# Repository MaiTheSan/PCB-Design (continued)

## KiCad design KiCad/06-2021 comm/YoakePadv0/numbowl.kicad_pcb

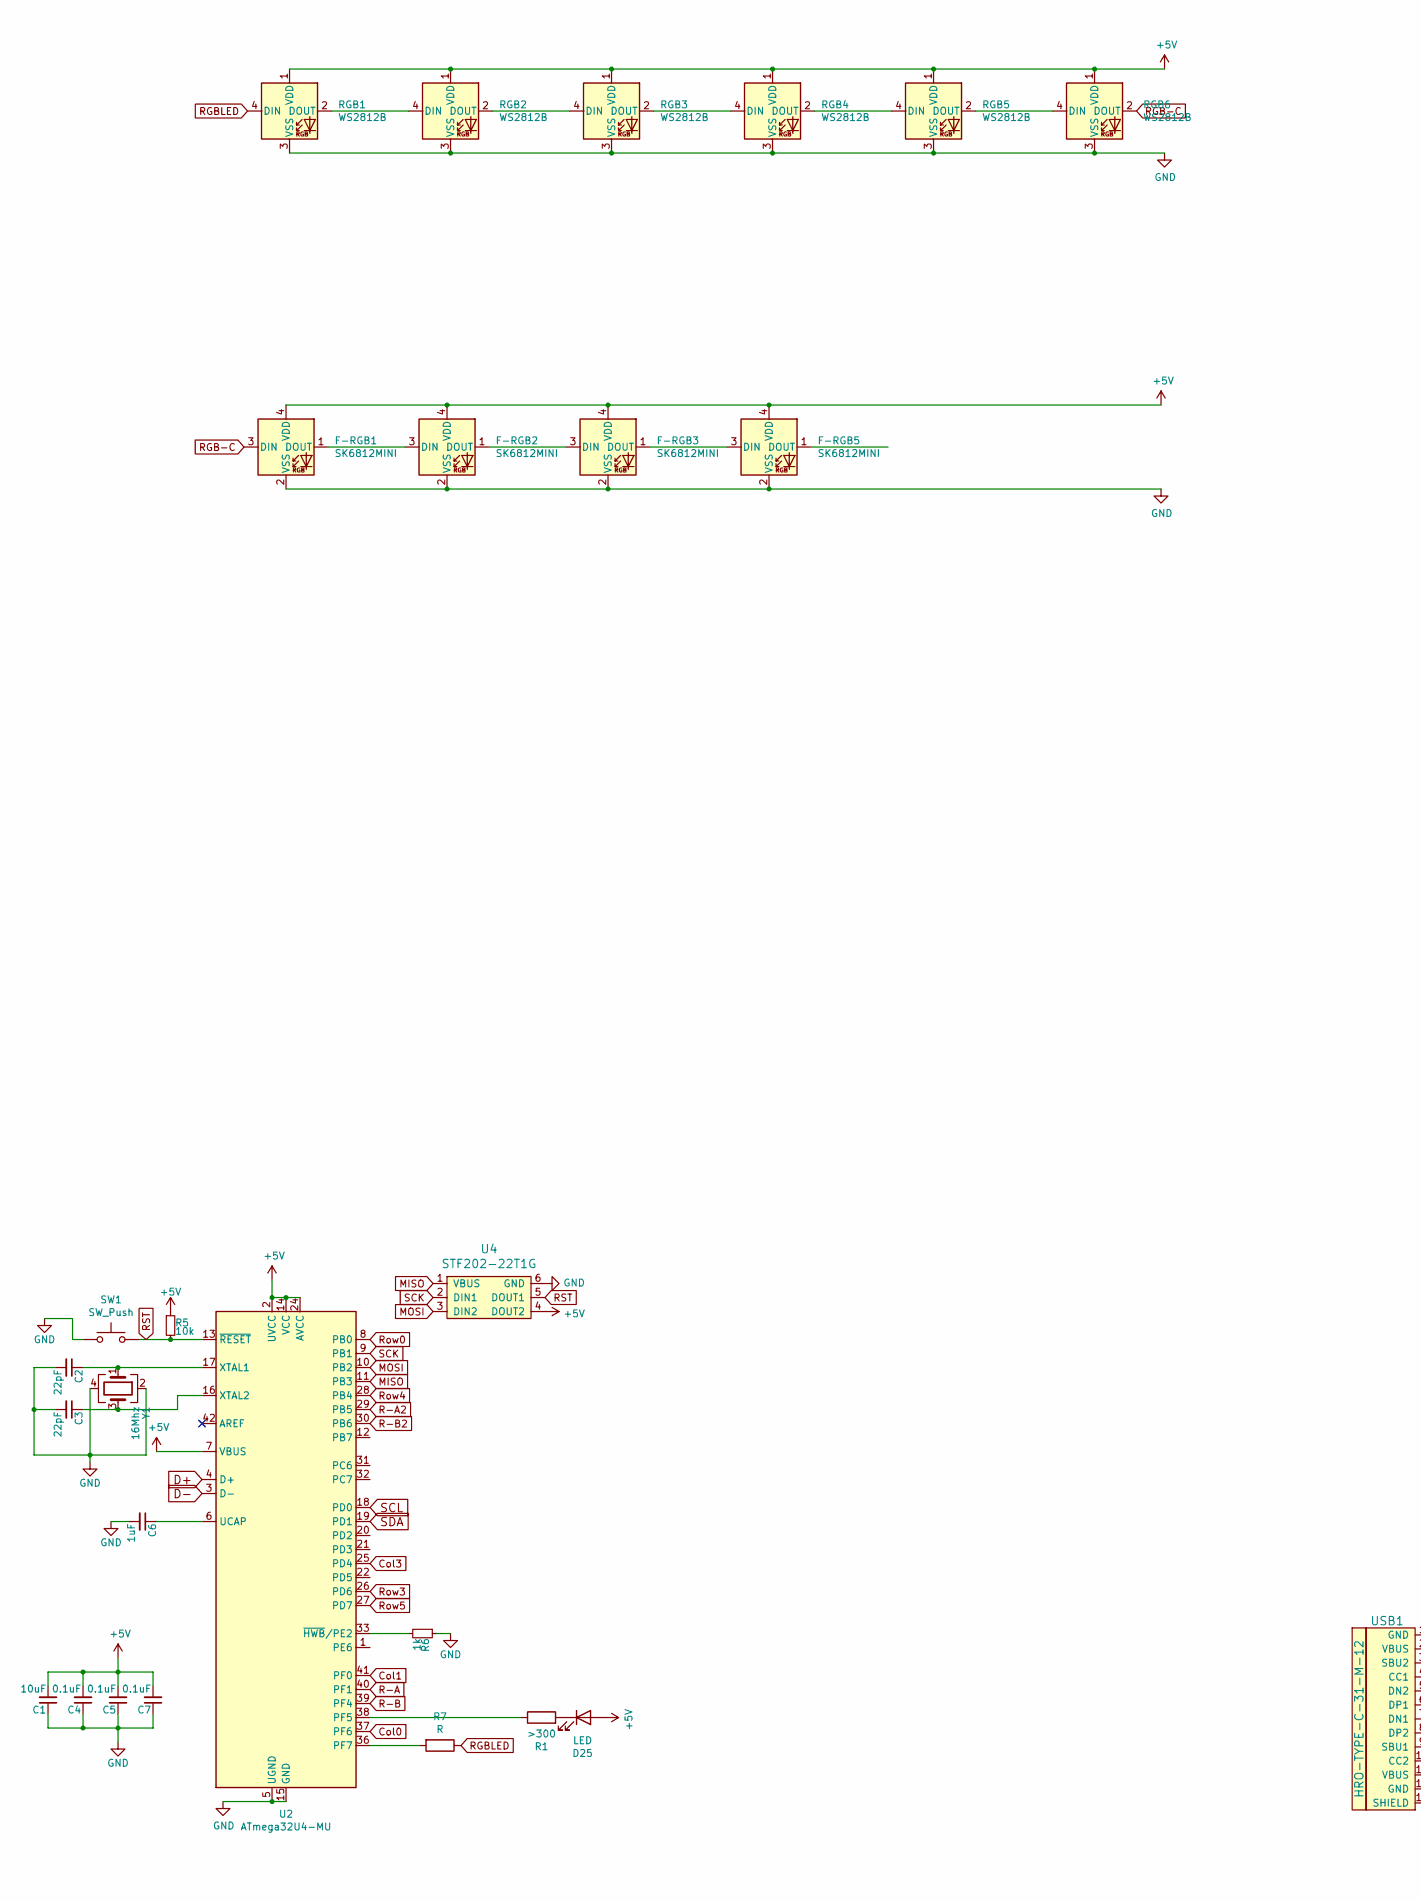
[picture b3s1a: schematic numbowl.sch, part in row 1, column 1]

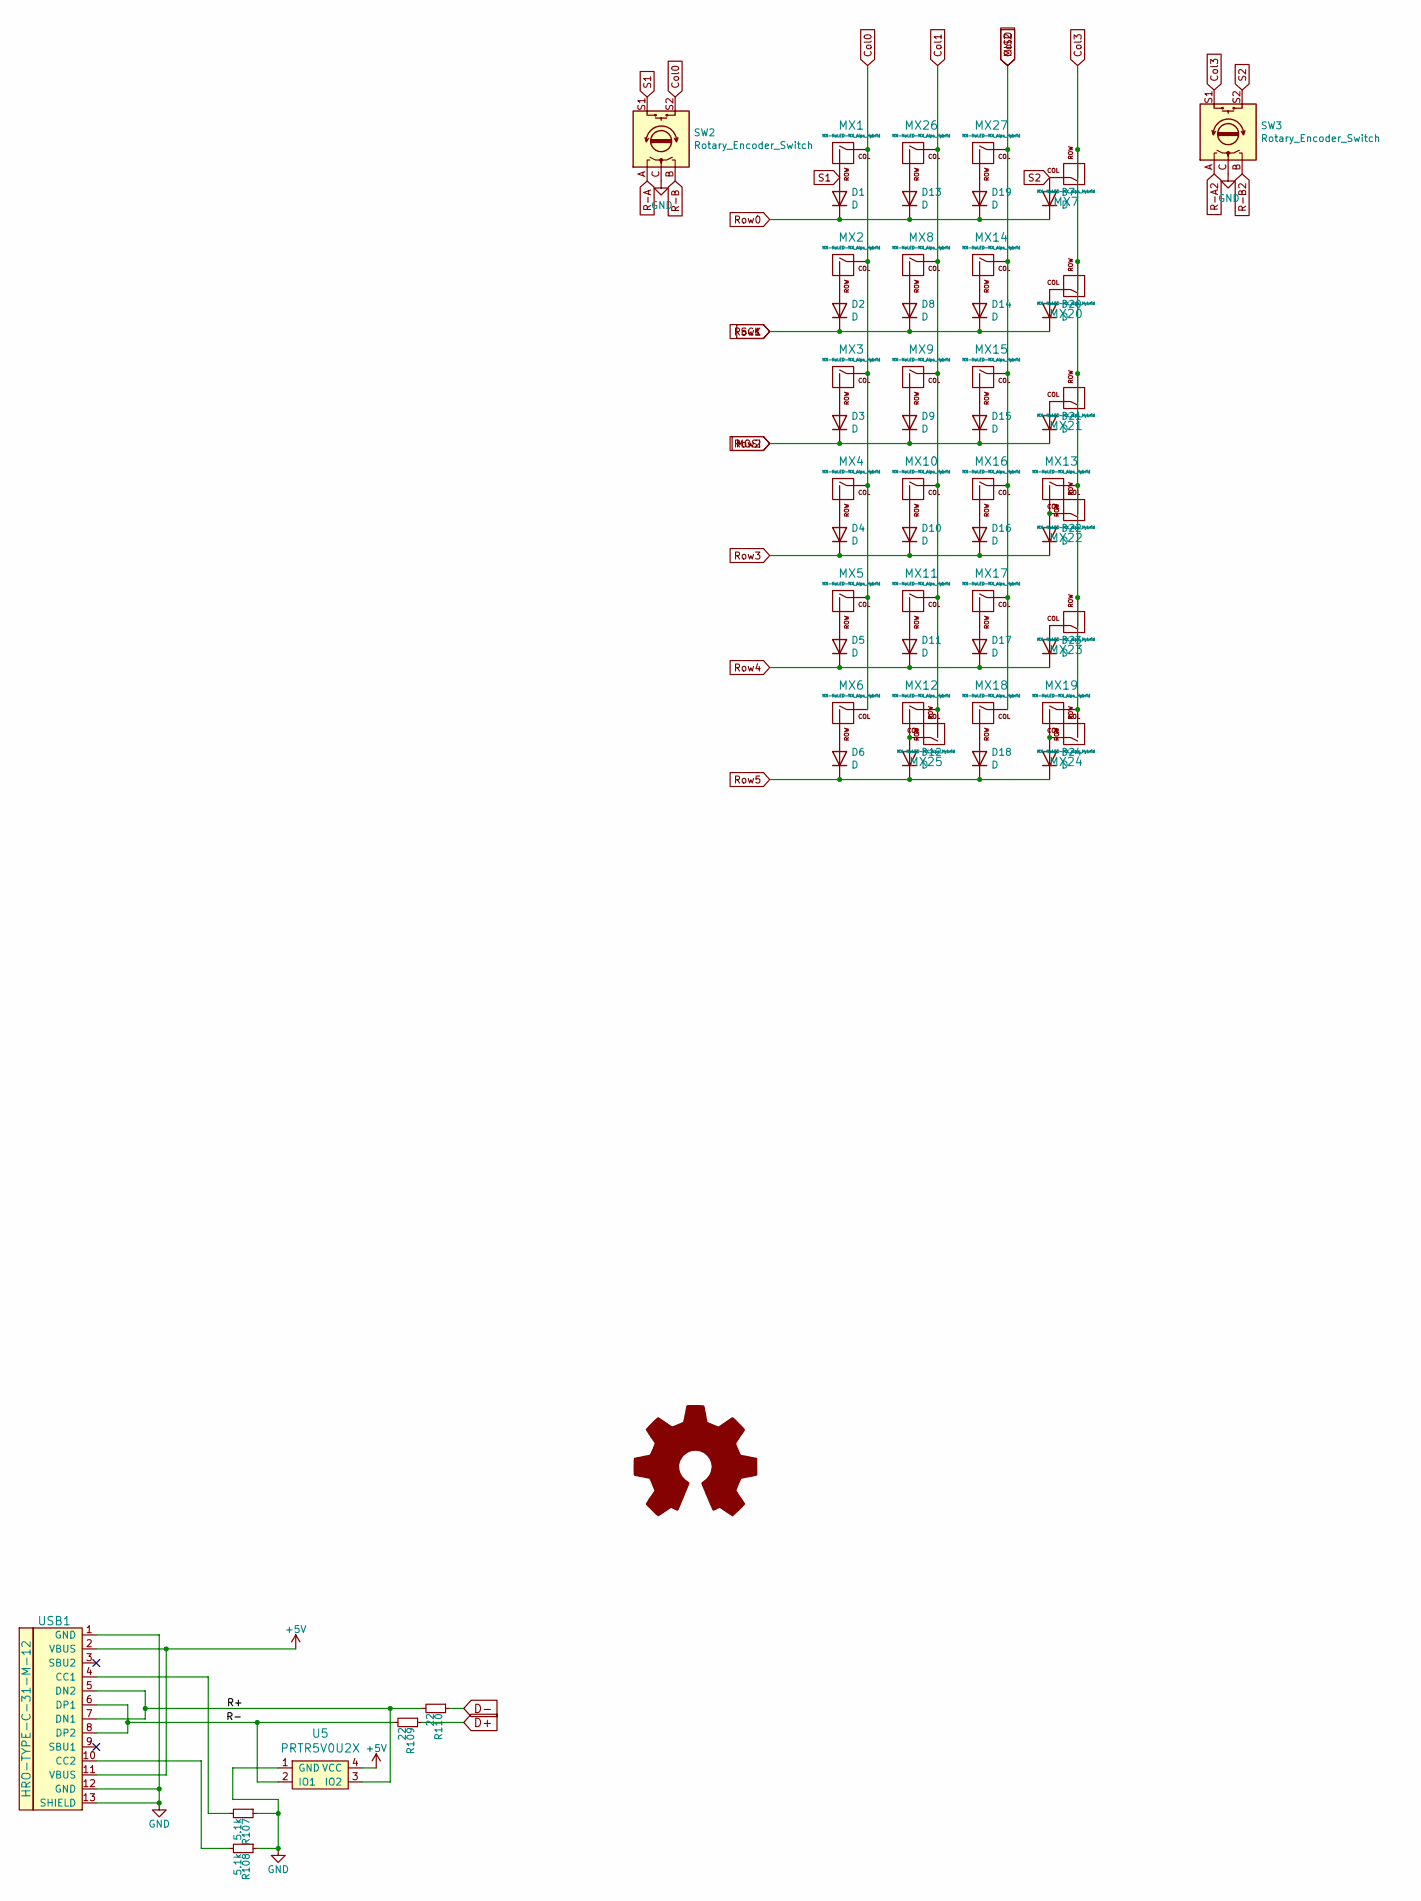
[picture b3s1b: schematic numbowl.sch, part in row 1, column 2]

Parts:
C1: 10uF; C_0603
C2, C3: 22pF; C_0603
C4, C5, C7: 0.1uF; C_0603
C6: 1uF; C_0603
D1, D2, D3, D4, D5, D6, D7, D8, D9, D10, D11, D12, D13, D14, D15, D16, D17, D18, D19, D20, D21, D22, D23, D24: D; D_SOD-123
D25: LED; MXOnly-LEDONLY
F-RGB1, F-RGB2, F-RGB3, F-RGB5: SK6812MINI; SK6812_Mini
LOGO1: Logo_Open_Hardware_Large; sanpjxlogo
MX1, MX2, MX3, MX4, MX5, MX6, MX7, MX8, MX9, MX10, MX11, MX12, MX14, MX15, MX16, MX17, MX18, MX20, MX21, MX22, MX23, MX24, MX26, MX27: MX-NoLED-MX_Alps_Hybrid; MXOnly-1U-NoLED
MX13, MX19: MX-NoLED-MX_Alps_Hybrid; MXOnly-2U-NoLED
MX25: MX-NoLED-MX_Alps_Hybrid; MXOnly-2U-ReversedStabilizers-NoLED
R1: >300; R_0805
R5: 10k; R_0805
R6: 1k; R_0805
R7: R; R_0805
R107, R108: 5.1k; R_0805
R109, R110: 22; R_0805
RGB1, RGB2, RGB3, RGB4, RGB5, RGB6: WS2812B; LED_WS2812B_PLCC4_5.0x5.0mm_P3.2mm
SW1: SW_Push; SKQG-1155865
SW2, SW3: Rotary_Encoder_Switch; RotaryEncoder_Alps_EC11E-Switch_Vertical_H20mm_Center
U2: ATmega32U4-MU; QFN-44-1EP_7x7mm_P0.5mm_EP5.15x5.15mm
U4: STF202-22T1G; Debuger
U5: PRTR5V0U2X; SOT143B
USB1: HRO-TYPE-C-31-M-12; HRO-TYPE-C-31-M-12-Assembly
Y1: 16Mhz; Crystal_SMD_3225-4Pin_3.2x2.5mm

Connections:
+5V: C1.2, C4.2, C5.2, C7.2, D25.2 (A), F-RGB1.4 (VDD), F-RGB2.4 (VDD), F-RGB3.4 (VDD), F-RGB5.4 (VDD), R5.1, RGB1.1 (VDD), RGB2.1 (VDD), RGB3.1 (VDD), RGB4.1 (VDD), RGB5.1 (VDD), RGB6.1 (VDD), U2.2 (UVCC), U2.7 (VBUS), U2.14 (VCC), U2.24 (AVCC), U2.34 (VCC), U2.44 (AVCC), U4.4 (DOUT2), U5.4 (VCC), USB1.2 (VBUS), USB1.11 (VBUS)
/R+: R110.2, U5.3 (IO2), USB1.5 (DN2), USB1.7 (DN1)
/R-: R109.2, U5.2 (IO1), USB1.6 (DP1), USB1.8 (DP2)
Col0: MX1.1 (COL), MX2.1 (COL), MX3.1 (COL), MX4.1 (COL), MX5.1 (COL), MX6.1 (COL), SW2.S2, U2.37 (PF6)
Col1: MX8.1 (COL), MX9.1 (COL), MX10.1 (COL), MX11.1 (COL), MX12.1 (COL), MX25.2 (ROW), MX26.1 (COL), U2.41 (PF0)
Col2: MX14.1 (COL), MX15.1 (COL), MX16.1 (COL), MX17.1 (COL), MX18.1 (COL), MX27.1 (COL), U2.11 (PB3), U4.1 (VBUS)
Col3: MX7.2 (ROW), MX13.1 (COL), MX19.1 (COL), MX20.2 (ROW), MX21.2 (ROW), MX22.2 (ROW), MX23.2 (ROW), MX24.2 (ROW), SW3.S1, U2.25 (PD4)
D+: R109.1, U2.4 (D+)
D-: R110.1, U2.3 (D-)
GND: C1.1, C2.2, C3.2, C4.1, C5.1, C6.2, C7.1, F-RGB1.2 (VSS), F-RGB2.2 (VSS), F-RGB3.2 (VSS), F-RGB5.2 (VSS), R6.1, R107.1, R108.1, RGB1.3 (VSS), RGB2.3 (VSS), RGB3.3 (VSS), RGB4.3 (VSS), RGB5.3 (VSS), RGB6.3 (VSS), SW1.1, SW2.C, SW3.C, U2.5 (UGND), U2.15 (GND), U2.23 (GND), U2.35 (GND), U2.43 (GND), U2.45 (GND), U4.6 (GND), U5.1 (GND), USB1.1 (GND), USB1.12 (GND), USB1.13 (SHIELD), Y1.2, Y1.4
MOSI: D3.1 (K), D9.1 (K), D15.1 (K), D21.1 (K), U2.10 (PB2), U4.3 (DIN2)
unnamed: C2.1, U2.17 (XTAL1), Y1.1
unnamed: C3.1, U2.16 (XTAL2), Y1.3
unnamed: C6.1, U2.6 (UCAP)
unnamed: D2.2 (A), MX2.2 (ROW)
unnamed: D3.2 (A), MX3.2 (ROW)
unnamed: D4.2 (A), MX4.2 (ROW)
unnamed: D5.2 (A), MX5.2 (ROW)
unnamed: D6.2 (A), MX6.2 (ROW)
unnamed: D8.2 (A), MX8.2 (ROW)
unnamed: D9.2 (A), MX9.2 (ROW)
unnamed: D10.2 (A), MX10.2 (ROW)
unnamed: D11.2 (A), MX11.2 (ROW)
unnamed: D12.2 (A), MX12.2 (ROW), MX25.1 (COL)
unnamed: D13.2 (A), MX26.2 (ROW)
unnamed: D14.2 (A), MX14.2 (ROW)
unnamed: D15.2 (A), MX15.2 (ROW)
unnamed: D16.2 (A), MX16.2 (ROW)
unnamed: D17.2 (A), MX17.2 (ROW)
unnamed: D18.2 (A), MX18.2 (ROW)
unnamed: D19.2 (A), MX27.2 (ROW)
unnamed: D20.2 (A), MX20.1 (COL)
unnamed: D21.2 (A), MX21.1 (COL)
unnamed: D22.2 (A), MX13.2 (ROW), MX22.1 (COL)
unnamed: D23.2 (A), MX23.1 (COL)
unnamed: D24.2 (A), MX19.2 (ROW), MX24.1 (COL)
unnamed: D25.1 (K), R1.2
unnamed: F-RGB1.1 (DOUT), F-RGB2.3 (DIN)
unnamed: F-RGB2.1 (DOUT), F-RGB3.3 (DIN)
unnamed: F-RGB3.1 (DOUT), F-RGB5.3 (DIN)
unnamed: R1.1, U2.38 (PF5)
unnamed: R6.2, U2.33 (~HWB~/PE2)
unnamed: R7.2, U2.36 (PF7)
unnamed: R107.2, USB1.4 (CC1)
unnamed: R108.2, USB1.10 (CC2)
unnamed: RGB1.2 (DOUT), RGB2.4 (DIN)
unnamed: RGB2.2 (DOUT), RGB3.4 (DIN)
unnamed: RGB3.2 (DOUT), RGB4.4 (DIN)
unnamed: RGB4.2 (DOUT), RGB5.4 (DIN)
unnamed: RGB5.2 (DOUT), RGB6.4 (DIN)
R-A: SW2.A, U2.40 (PF1)
R-A2: SW3.A, U2.29 (PB5)
R-B: SW2.B, U2.39 (PF4)
R-B2: SW3.B, U2.30 (PB6)
RGB-C: F-RGB1.3 (DIN), RGB6.2 (DOUT)
RGBLED: R7.1, RGB1.4 (DIN)
RST: R5.2, SW1.2, U2.13 (~RESET), U4.5 (DOUT1)
Row0: D1.1 (K), D7.1 (K), D13.1 (K), D19.1 (K), U2.8 (PB0)
Row1: D2.1 (K), D8.1 (K), D14.1 (K), D20.1 (K), U2.9 (PB1), U4.2 (DIN1)
Row3: D4.1 (K), D10.1 (K), D16.1 (K), D22.1 (K), U2.26 (PD6)
Row4: D5.1 (K), D11.1 (K), D17.1 (K), D23.1 (K), U2.28 (PB4)
Row5: D6.1 (K), D12.1 (K), D18.1 (K), D24.1 (K), U2.27 (PD7)
S1: D1.2 (A), MX1.2 (ROW), SW2.S1
S2: D7.2 (A), MX7.1 (COL), SW3.S2
SCL: U2.18 (PD0)
SDA: U2.19 (PD1)

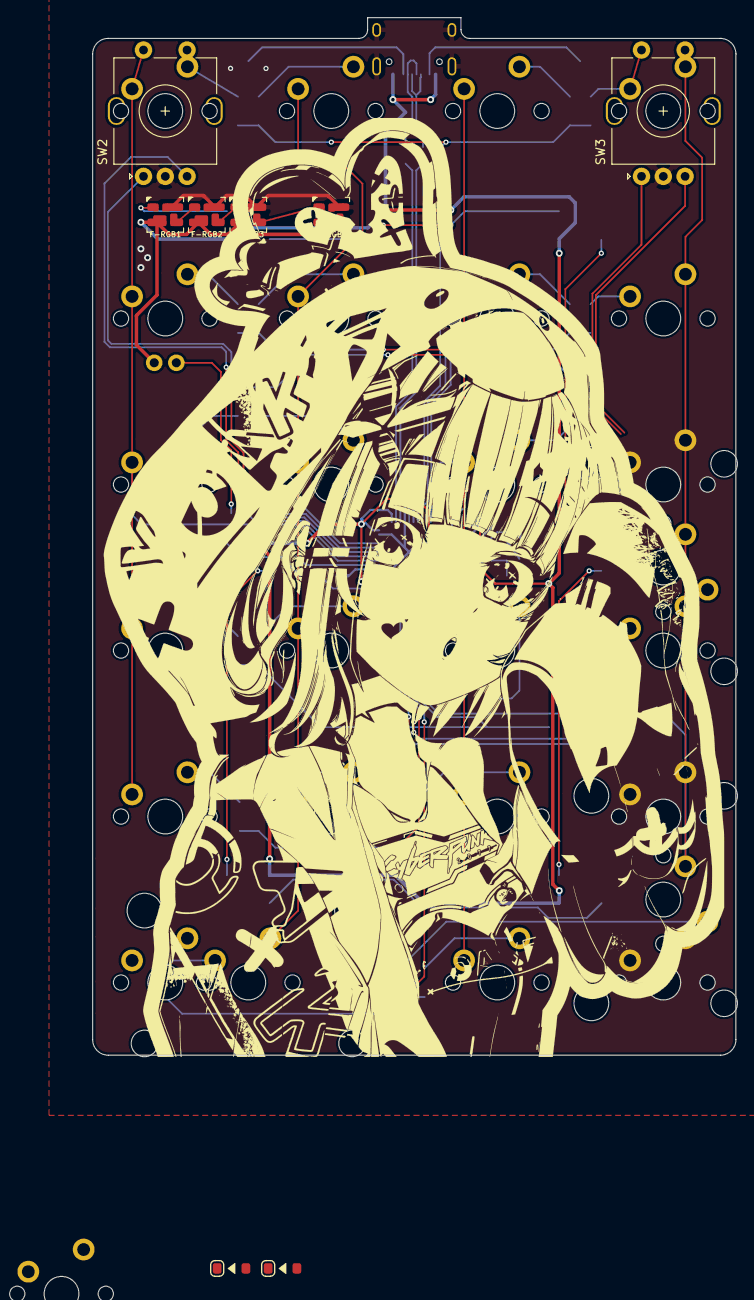
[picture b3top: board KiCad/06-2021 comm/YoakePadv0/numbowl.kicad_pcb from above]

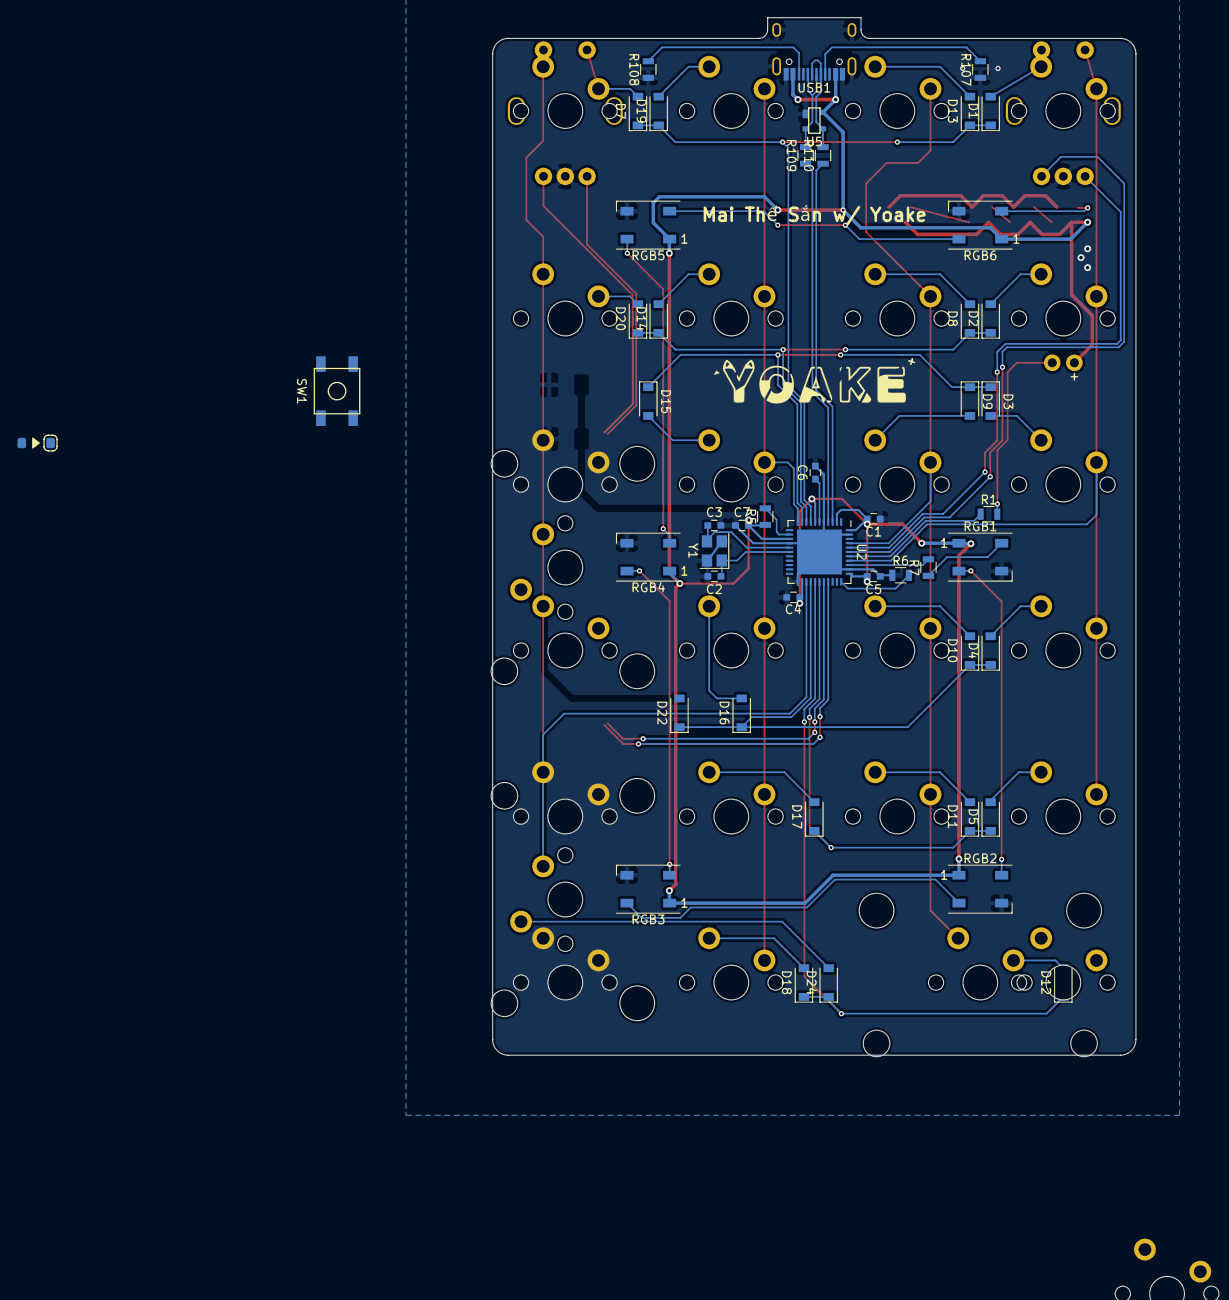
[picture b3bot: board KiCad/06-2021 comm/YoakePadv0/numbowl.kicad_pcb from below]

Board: 2 copper layers, 73.8 x 119.1 mm, 84 parts (48 on the bottom side), 64 nets.

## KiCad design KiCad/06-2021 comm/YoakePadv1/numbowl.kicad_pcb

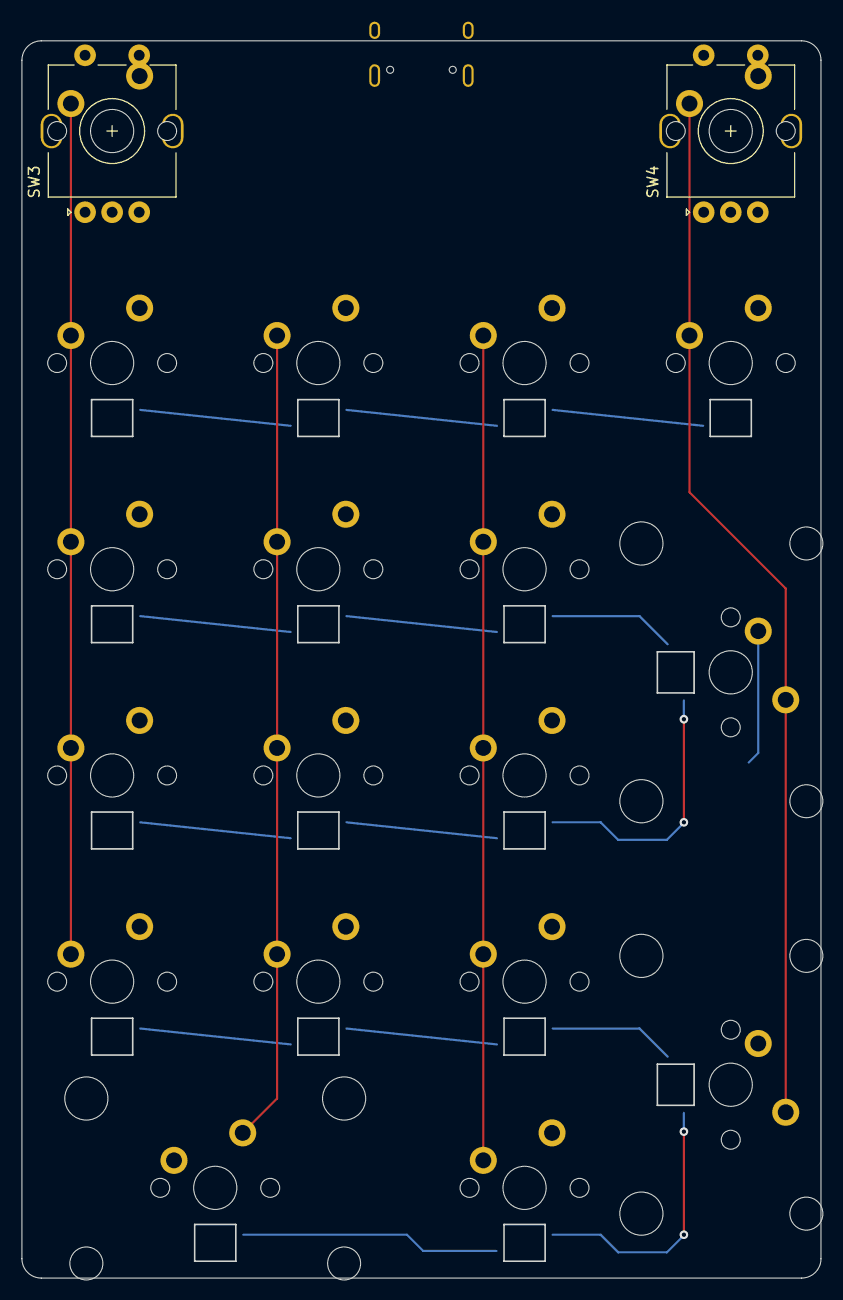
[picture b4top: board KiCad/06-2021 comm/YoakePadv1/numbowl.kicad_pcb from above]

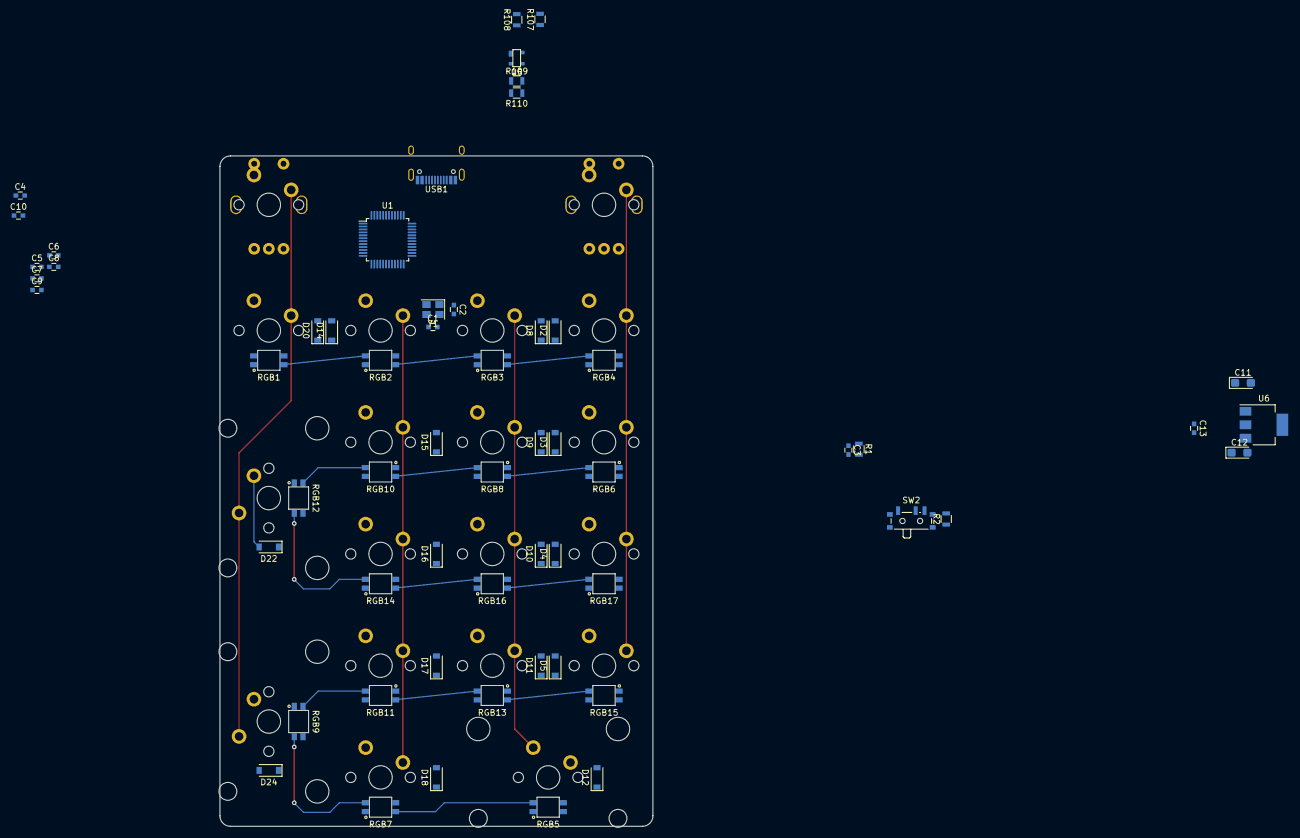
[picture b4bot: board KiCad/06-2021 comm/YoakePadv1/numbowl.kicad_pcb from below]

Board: 2 copper layers, 73.8 x 114.3 mm, 80 parts (59 on the bottom side), 56 nets.

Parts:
C1, C2: 22pF; C_0603
C3, C5, C6, C7, C9, C13: 0.1uF; C_0603
C4: 10uF; C_0603
C8: 10nF; C_0603
C10: 1uF; C_0603
C11, C12: >=22uF; CP_EIA-3216-12_Kemet-S
D2, D3, D4, D5, D8, D9, D10, D11, D12, D14, D15, D16, D17, D18, D20, D22, D24: D; D_SOD-123
MX1, MX2, MX3, MX4, MX5, MX7, MX8, MX9, MX10, MX11, MX14, MX15, MX16, MX17, MX18, MX20: MX-NoLED-MX_Alps_Hybrid; MXOnly-1U-NoLED
MX13, MX19: MX-NoLED-MX_Alps_Hybrid; MXOnly-2U-NoLED
MX25: MX-NoLED-MX_Alps_Hybrid; MXOnly-2U-ReversedStabilizers-NoLED
R1, R2: 10k; R_0805
R107, R108: 5.1k; R_0805
R109, R110: 22; R_0805
RGB1, RGB2, RGB3, RGB4, RGB5, RGB7, RGB14, RGB16, RGB17: WS2812B; RGB-6028
RGB6, RGB8, RGB9, RGB10, RGB11, RGB12, RGB13, RGB15: WS2812B; RGB-6028_FLIPPED
SW2: SW_SPDT; SW_SPDT_PCM12
SW3, SW4: Rotary_Encoder_Switch; RotaryEncoder_Alps_EC11E-Switch_Vertical_H20mm_Center
U1: STM32F303CCTx; LQFP-48_7x7mm_P0.5mm
U5: PRTR5V0U2X; SOT143B
U6: AMS1117-3.3; SOT-223-3_TabPin2
USB1: HRO-TYPE-C-31-M-12; HRO-TYPE-C-31-M-12-Assembly
Y1: 16Mhz; Crystal_SMD_3225-4Pin_3.2x2.5mm

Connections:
+5V: C11.1, RGB1.1, RGB2.1, RGB3.1, RGB4.1, RGB5.1, RGB6.1, RGB7.1, RGB8.1, RGB9.1, RGB10.1, RGB11.1, RGB12.1, RGB13.1, RGB14.1, RGB15.1, RGB16.1, RGB17.1, U5.4, U6.3, USB1.2, USB1.11
/R+: R110.2, U5.3, USB1.5, USB1.7
/R-: R109.2, U5.2, USB1.6, USB1.8
Boot0: R2.1, SW2.2
D+: R109.1, U1.33
D-: R110.1, U1.32
GND: C1.2, C2.2, C3.2, C4.1, C5.1, C6.1, C7.1, C8.1, C9.1, C10.1, C11.2, C12.2, C13.1, R107.1, R108.1, RGB1.3, RGB2.3, RGB3.3, RGB4.3, RGB5.3, RGB6.3, RGB7.3, RGB8.3, RGB9.3, RGB10.3, RGB11.3, RGB12.3, RGB13.3, RGB14.3, RGB15.3, RGB16.3, RGB17.3, SW2.1, U1.8, U1.23, U1.35, U1.47, U5.1, U6.1, USB1.1, USB1.12, USB1.13, Y1.2, Y1.4
unnamed: C1.1, U1.5, Y1.3
unnamed: C2.1, U1.6, Y1.1
unnamed: C3.1, R1.2, U1.7
unnamed: D2.2, MX2.2
unnamed: D3.2, MX3.2
unnamed: D4.2, MX4.2
unnamed: D5.2, MX5.2
unnamed: D8.2, MX8.2
unnamed: D9.2, MX9.2
unnamed: D4.1, D10.1, D16.1, D22.1
unnamed: D10.2, MX10.2
unnamed: D5.1, D11.1, D17.1
unnamed: D11.2, MX11.2
unnamed: D12.1, D18.1, D24.1
unnamed: D12.2, MX25.1
unnamed: D2.1, D8.1, D14.1, D20.1
unnamed: D14.2, MX14.2
unnamed: D3.1, D9.1, D15.1
unnamed: D15.2, MX15.2
unnamed: D16.2, MX16.2
unnamed: D17.2, MX17.2
unnamed: D18.2, MX18.2
unnamed: D20.2, MX20.2
unnamed: D22.2, MX13.1
unnamed: D24.2, MX19.1
unnamed: MX1.1, MX2.1, MX3.1, MX4.1, MX5.1
unnamed: MX8.1, MX9.1, MX10.1, MX11.1, MX25.2
unnamed: MX7.1, MX13.2, MX19.2, MX20.1
unnamed: MX14.1, MX15.1, MX16.1, MX17.1, MX18.1
unnamed: R2.2, U1.44
unnamed: R107.2, USB1.4
unnamed: R108.2, USB1.10
unnamed: RGB1.2, RGB2.4
unnamed: RGB2.2, RGB3.4
unnamed: RGB3.2, RGB4.4
unnamed: RGB4.2, RGB6.4
unnamed: RGB5.4, RGB7.2
unnamed: RGB6.2, RGB8.4
unnamed: RGB7.4, RGB9.2
unnamed: RGB10.2, RGB12.4
unnamed: RGB8.2, RGB10.4
unnamed: RGB9.4, RGB11.2
unnamed: RGB11.4, RGB13.2
unnamed: RGB12.2, RGB14.4
unnamed: RGB13.4, RGB15.2
unnamed: RGB14.2, RGB16.4
unnamed: RGB15.4, RGB17.2
unnamed: RGB16.2, RGB17.4
VCC: C4.2, C5.2, C6.2, C7.2, C8.2, C9.2, C10.2, C12.1, C13.2, R1.1, SW2.3, U1.1, U1.9, U1.24, U1.36, U1.48, U6.2
